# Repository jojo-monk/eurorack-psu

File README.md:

# Eurorack PSU

DIY Eurorack power supply based on three **Mean Well IRM AC/DC modules**, with linear post-regulation using **LM350** and **LM337**.

The design was developed in **KiCad** specifically for Eurorack modular synthesizers, with separate power sources for the positive and negative rails and a dedicated +5 V supply.

## Features

- **+12 V / -12 V / +5 V** Eurorack power rails
- 3× isolated Mean Well IRM AC/DC modules
- Linear regulation of the ±12 V rails
- **LM350** positive voltage regulator
- **LM337** negative voltage regulator
- Dedicated +5 V supply
- Filtering and decoupling
- Heatsinks on the linear regulators
- KiCad schematic and PCB design

## Power supply architecture

The power supply uses three independent Mean Well AC/DC modules:

```text
                         AC MAINS
                            │
             ┌──────────────┼──────────────┐
             │              │              │
             ▼              ▼              ▼
        IRM-45-15       IRM-20-15       IRM-20-5
          15 V / 3 A      15 V / 1.4 A     5 V / 4 A
             │              │              │
             ▼              ▼              │
           LM350          LM337             │
             │              │              │
             ▼              ▼              ▼
           +12 V           -12 V           +5 V
             │              │              │
             └──────────────┴──────────────┘
                            │
                     Eurorack power bus
```

The two 15 V supplies are used independently for the positive and negative Eurorack rails.

The ±12 V outputs are obtained through linear regulation, providing additional filtering and regulation after the isolated AC/DC conversion stage.

## Mean Well modules

| Module | Output | Rated current | Rated power | Rail |
|---|---:|---:|---:|---|
| **IRM-45-15** | 15 V DC | 3 A | 45 W | +12 V |
| **IRM-20-15** | 15 V DC | 1.4 A | 21 W | -12 V |
| **IRM-20-5** | 5 V DC | 4 A | 20 W | +5 V |

The three AC/DC modules provide a combined nominal power of approximately **86 W** before linear regulation losses.

## Output specifications

| Rail | Regulation | Maximum current* | Maximum output power* |
|---|---|---:|---:|
| **+12 V** | LM350 | 3 A | 36 W |
| **-12 V** | LM337 | 1.4 A | 16.8 W |
| **+5 V** | IRM-20-5 | 4 A | 20 W |
| **Total** | | | **72.8 W** |

\* The values for the ±12 V rails are theoretical maximums based on the nominal output current of the corresponding Mean Well modules. Actual continuous output capability depends on thermal conditions, heatsink installation, PCB design and ambient temperature.

## Thermal considerations

The ±12 V rails use linear regulators, which dissipate the voltage difference between the 15 V input and the regulated 12 V output as heat.

## PCB

The PCB was designed using **KiCad**.

The repository contains the design files and manufacturing data for the power supply.

## Interactive BOM

The interactive Bill of Materials is available online:

**[🔧 Open Interactive BOM](https://jojo-monk.github.io/eurorack-psu/ibom.html)**

## Project status

**Built, tested and fully functional.**

The power supply has been successfully assembled, tested and validated in operation. All three output rails (**+12 V, -12 V and +5 V**) have been tested and the power supply is fully operational in a Eurorack system.

## Safety

> [!WARNING]
> **MAINS VOLTAGE**
>
> This power supply is directly connected to the AC mains.
>
> Mains voltage can cause serious injury or death. This project should only be built and tested by people familiar with mains electrical safety.
>
> The finished power supply must be installed in a suitable enclosure with:
>
> - proper mains insulation
> - protective earth where required
> - appropriate fusing
> - strain relief
> - adequate spacing between mains and low-voltage circuitry
> - protection against accidental contact with mains voltage
>
> Do not operate the PCB exposed when connected to the mains.

## Project status

This is a DIY Eurorack power supply developed for personal experimentation and modular synthesizer projects.

The design is provided as-is. Always verify the actual output voltages, current capability and thermal performance of the assembled unit before connecting Eurorack modules.

## License

License
This project is licensed under the Creative Commons Attribution-NonCommercial-ShareAlike 4.0 International (CC BY-NC-SA 4.0) license.
Copyright © 2026 Johann Moine
You are free to:
Share — copy and redistribute the material
Adapt — remix, transform and build upon the material
Under the following conditions:
Attribution — You must give appropriate credit to the original author, provide a link to the license, and indicate if changes were made.
NonCommercial — You may not use the material for commercial purposes.
ShareAlike — If you remix, transform, or build upon the material, you must distribute your contributions under the same license.
See the full license:
Creative Commons BY-NC-SA 4.0

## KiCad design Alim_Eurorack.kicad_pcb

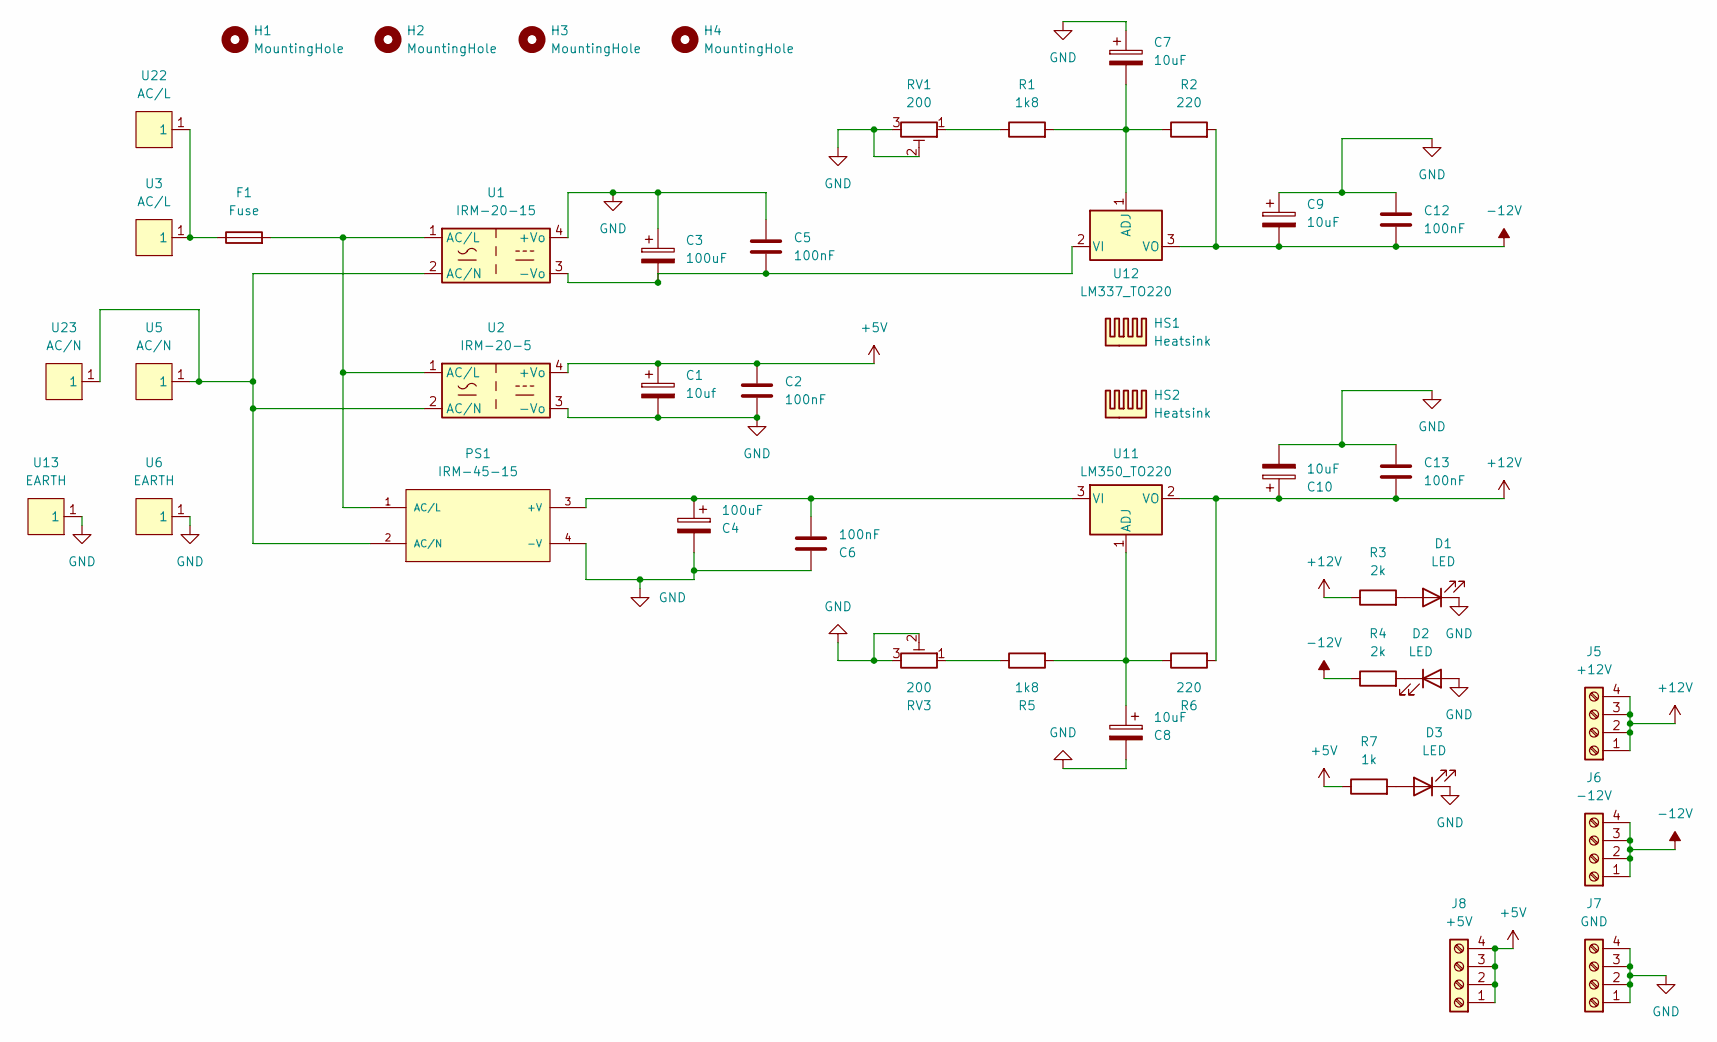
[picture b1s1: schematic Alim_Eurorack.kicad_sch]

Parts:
C1: 10uf; CP_Radial_D5.0mm_P2.00mm
C2, C5, C6, C12, C13: 100nF; Capacitor_Disc_D3.8mm_W2.6mm_P2.50mm
C3, C4: 100uF; CP_Radial_D7.5mm_P2.50mm
C7, C8, C9, C10: 10uF; CP_Radial_D5.0mm_P2.00mm
D1, D2, D3: LED; LED_D3.0mm
F1: Fuse; Fuseholder_Cylinder-5x20mm_Schurter_0031_8201_Horizontal_Op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
H1, H2, H3, H4: MountingHole; MountingHole_3.2mm_M3
HS1, HS2: Heatsink; Heatsink_Fischer_SK129-STS_42x25mm_2xDrill2.5mm
J5: +12V; TerminalBlock_RND_205-00047_1x04_P5.00mm_Horizontal
J6: -12V; TerminalBlock_RND_205-00047_1x04_P5.00mm_Horizontal
J7: GND; TerminalBlock_RND_205-00047_1x04_P5.00mm_Horizontal
J8: +5V; TerminalBlock_RND_205-00047_1x04_P5.00mm_Horizontal
PS1: IRM-45-15; CONV_IRM-45-15
R1, R5: 1k8; R_Axial_DIN0207_L6.3mm_D2.5mm_P10.16mm_Horizontal
R2, R6: 220; R_Axial_DIN0207_L6.3mm_D2.5mm_P10.16mm_Horizontal
R3, R4: 2k; R_Axial_DIN0207_L6.3mm_D2.5mm_P10.16mm_Horizontal
R7: 1k; R_Axial_DIN0207_L6.3mm_D2.5mm_P10.16mm_Horizontal
RV1, RV3: 200; Potentiometer_Bourns_3299Y_Vertical
U1: IRM-20-15; Converter_ACDC_MeanWell_IRM-20-xx_THT
U2: IRM-20-5; Converter_ACDC_MeanWell_IRM-20-xx_THT
U3, U22: AC/L; CONN-TH_726386-2; MPN 726386-2; LCSC Part C305817
U5, U23: AC/N; CONN-TH_726386-2; MPN 726386-2; LCSC Part C305817
U6, U13: EARTH; CONN-TH_726386-2; MPN 726386-2; LCSC Part C305817
U11: LM350_TO220; TO-220-3_Vertical
U12: LM337_TO220; TO-220-3_Vertical

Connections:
+5V: C1.1, C2.1, J8.1, J8.2, J8.3, J8.4, R7.1, U2.4 (+Vo)
+12V: C10.1, C13.2, J5.1, J5.2, J5.3, J5.4, R3.1, R6.2, U11.2 (VO)
-12V: C9.2, C12.2, J6.1, J6.2, J6.3, J6.4, R2.2, R4.1, U12.3 (VO)
GND: C1.2, C2.2, C3.1, C4.2, C5.1, C6.1, C7.1, C8.2, C9.1, C10.2, C12.1, C13.1, D1.1 (K), D2.2 (A), D3.1 (K), J7.1, J7.2, J7.3, J7.4, PS1.4 (-V), RV1.2, RV1.3, RV3.2, RV3.3, U1.4 (+Vo), U2.3 (-Vo), U6.1 (1_1), U13.1 (1_1)
unnamed: D1.2 (A), R3.2
unnamed: D2.1 (K), R4.2
unnamed: D3.2 (A), R7.2
unnamed: F1.1, U3.1 (1_1), U22.1 (1_1)
unnamed: C4.1, C6.2, PS1.3 (+V), U11.3 (VI)
unnamed: F1.2, PS1.1 (AC/L), U1.1 (AC/L), U2.1 (AC/L)
unnamed: PS1.2 (AC/N), U1.2 (AC/N), U2.2 (AC/N), U5.1 (1_1), U23.1 (1_1)
unnamed: R1.1, RV1.1
unnamed: R5.1, RV3.1
unnamed: C3.2, C5.2, U1.3 (-Vo), U12.2 (VI)
unnamed: C8.1, R5.2, R6.1, U11.1 (ADJ)
unnamed: C7.2, R1.2, R2.1, U12.1 (ADJ)

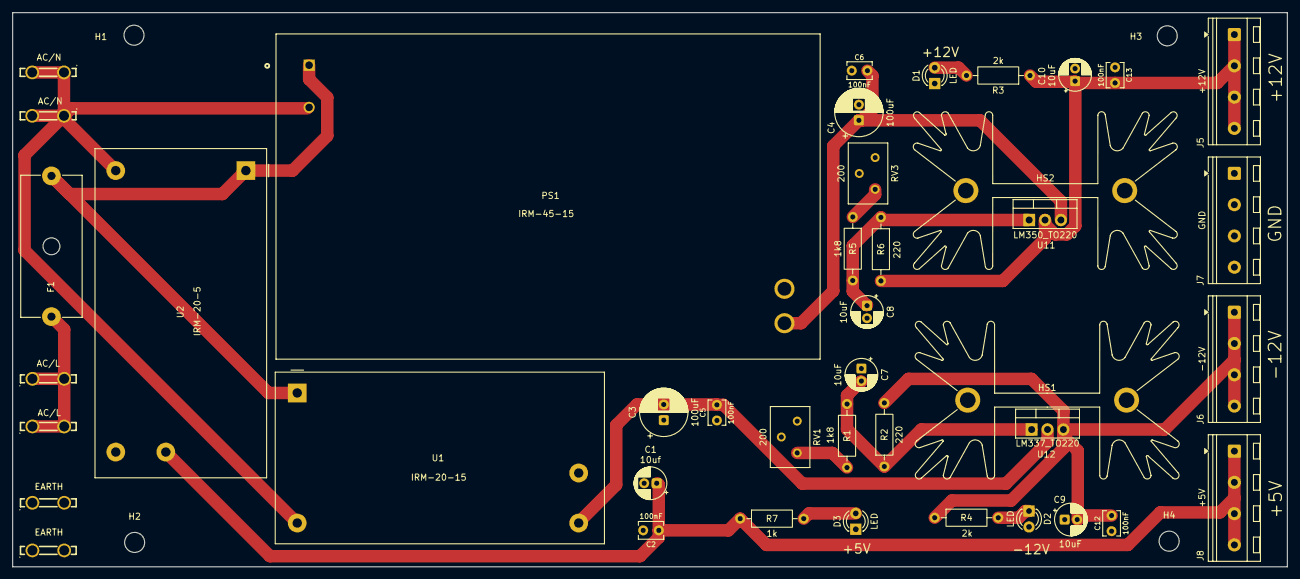
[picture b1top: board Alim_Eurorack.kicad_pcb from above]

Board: 2 copper layers, 203.8 x 88.6 mm, 46 parts (0 on the bottom side), 16 nets.

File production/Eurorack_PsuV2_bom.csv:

Designator,Footprint,Quantity,Value,LCSC Part #
"C1, C10, C7, C8, C9",CP_Radial_D5.0mm_P2.00mm,5,10uf,
"C12, C13, C2, C5, C6",Capacitor_Disc_D3.8mm_W2.6mm_P2.50mm,5,100nF,
"C3, C4",CP_Radial_D7.5mm_P2.50mm,2,100uF,
"D1, D2, D3",LED_D3.0mm,3,LED,
F1,Fuseholder_Cylinder-5x20mm_Schurter_0031_8201_Horizontal_Open,1,Fuse,
"HS1, HS2",Heatsink_Fischer_SK129-STS_42x25mm_2xDrill2.5mm,2,Heatsink,
J1,TerminalBlock_RND_205-00002_1x03_P5.00mm_Horizontal,1,+12V,
J2,TerminalBlock_RND_205-00002_1x03_P5.00mm_Horizontal,1,-12V,
J3,TerminalBlock_RND_205-00002_1x03_P5.00mm_Horizontal,1,GND,
J4,TerminalBlock_RND_205-00002_1x03_P5.00mm_Horizontal,1,+5V,
PS1,CONV_IRM-45-15,1,IRM-45-15,
"R1, R5",R_Axial_DIN0207_L6.3mm_D2.5mm_P10.16mm_Horizontal,2,1k8,
"R2, R6",R_Axial_DIN0207_L6.3mm_D2.5mm_P10.16mm_Horizontal,2,220,
"R3, R4",R_Axial_DIN0207_L6.3mm_D2.5mm_P10.16mm_Horizontal,2,2k,
R7,R_Axial_DIN0207_L6.3mm_D2.5mm_P10.16mm_Horizontal,1,1k,
"RV1, RV3",Potentiometer_Bourns_3299Y_Vertical,2,200,
U1,Converter_ACDC_MeanWell_IRM-20-xx_THT,1,IRM-20-15,
U11,TO-220-3_Vertical,1,LM350_TO220,
U12,TO-220-3_Vertical,1,LM337_TO220,
"U13, U6",CONN-TH_726386-2,2,EARTH,C305817
U2,Converter_ACDC_MeanWell_IRM-20-xx_THT,1,IRM-20-5,
"U22, U3",CONN-TH_726386-2,2,AC/L,C305817
"U23, U5",CONN-TH_726386-2,2,AC/N,C305817
